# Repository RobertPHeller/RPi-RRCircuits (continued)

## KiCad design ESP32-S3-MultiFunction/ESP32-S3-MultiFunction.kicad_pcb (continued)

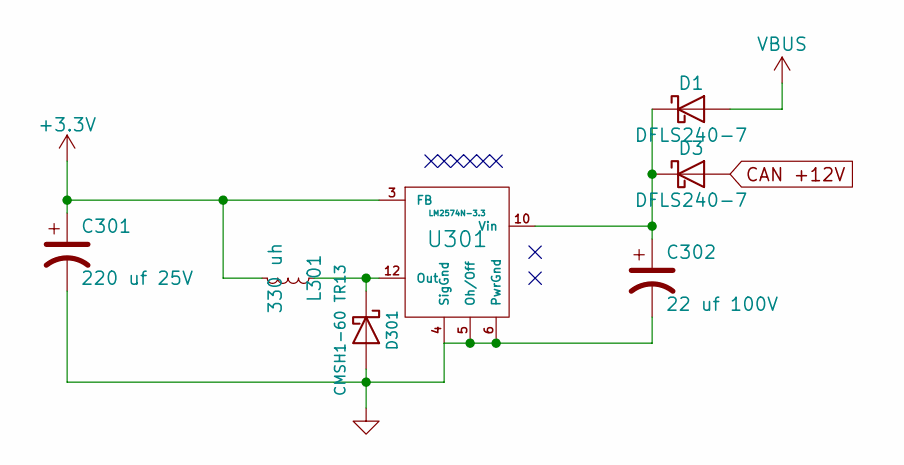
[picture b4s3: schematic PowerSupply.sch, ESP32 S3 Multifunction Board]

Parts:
C301: 220 uf 25V; CP_Elec_8x10; Mouser Part Number 647-UWT1E221MNL1GS
C302: 22 uf 100V; CP_Elec_8x10; Mouser Part Number 647-UUX2A220MNL6GS
D1, D3: DFLS240-7; D_PowerDI-123; Mouser Part Number 621-DFLS240-7
D301: CMSH1-60 TR13; D_SMB; Mouser Part Number 610-CMSH1-60TR13
L301: 330 uh; SRN1060; Mouser Part Number 652-SRN1060-331M
U301: LM2574N-3.3; SOIC-14_7.4x8.7mm_Pitch1.27mm; Mouser Part Number 926-LM2574MX33NOPB

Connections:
CAN +12V: D3.2 (A); also elsewhere on the board
GND: C301.2, C302.2, D301.2 (A), U301.4 (SigGnd), U301.5 (Oh/Off), U301.6 (PwrGnd); also elsewhere on the board
unnamed: C302.1, D1.1 (K), D3.1 (K), U301.10 (Vin)
unnamed: D301.1 (K), L301.1, U301.12 (Out)
VBUS: D1.2 (A); also elsewhere on the board

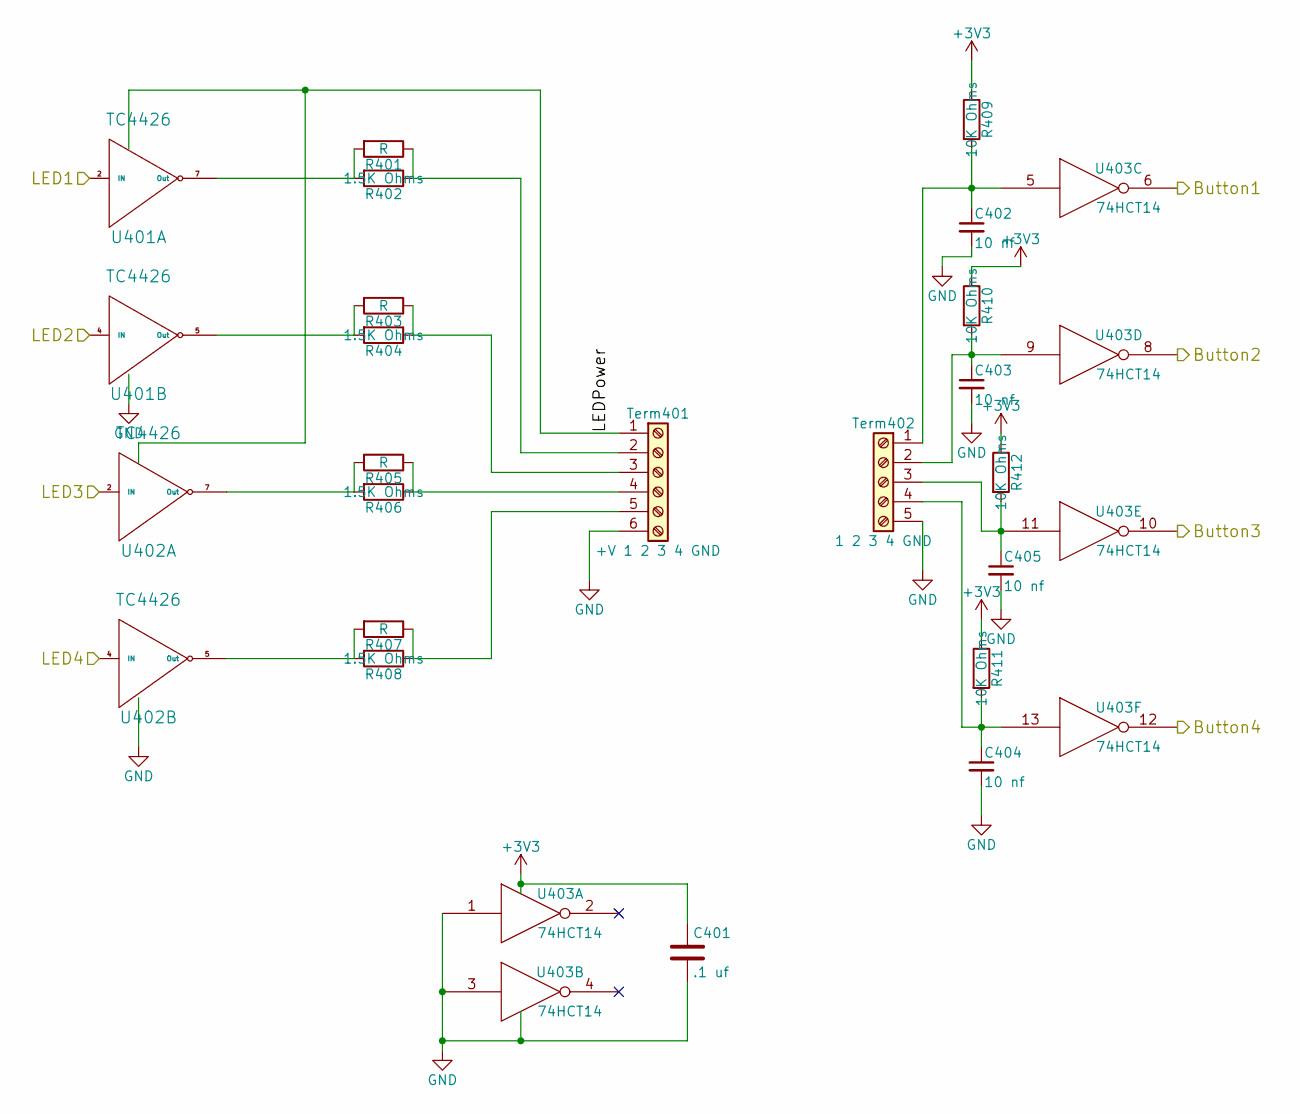
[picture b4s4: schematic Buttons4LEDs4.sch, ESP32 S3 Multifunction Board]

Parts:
C401: .1 uf; C_0603; Mouser Part Number 710-885012206095
C402, C403, C404, C405: 10 nf; C_0603; Mouser Part Number 710-885382206002
R401, R403, R405, R407: R; R_Axial_DIN0207_L6.3mm_D2.5mm_P7.62mm_Horizontal
R402, R404, R406, R408: 1.5K Ohms; R_0603; Mouser Part Number 71-CRCW06031K50JNEAC
R409, R410, R411, R412: 10K Ohms; R_0603; Mouser Part Number 71-CRCW060310K0JNEBC
Term401: +V 1 2 3 4 GND; TerminalBlock_Pheonix_MPT-2.54mm_6pol; Mouser Part Number 651-1725698
Term402: 1 2 3 4 GND; TerminalBlock_Pheonix_MPT-2.54mm_5pol; Mouser Part Number 651-1725685
U401, U402: TC4426; SOIC-8_3.9x4.9mm_Pitch1.27mm; Mouser Part Number 579-TC1426COA713
U403: 74HCT14; SOIC-14_3.9x8.7mm_Pitch1.27mm; Mouser Part Number 595-CD74HC14M

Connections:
/Buttons and LEDs/Button1: U403.6; also elsewhere on the board
/Buttons and LEDs/Button2: U403.8; also elsewhere on the board
/Buttons and LEDs/Button3: U403.10; also elsewhere on the board
/Buttons and LEDs/Button4: U403.12; also elsewhere on the board
/ESP32 MCU/GPIO1(LEDS4): U402.4 (IN); also elsewhere on the board
/ESP32 MCU/GPIO17(LEDS1): U401.2 (IN); also elsewhere on the board
/ESP32 MCU/GPIO18(LEDS2): U401.4 (IN); also elsewhere on the board
/ESP32 MCU/GPIO21(LEDS3): U402.2 (IN); also elsewhere on the board
GND: C401.2, C402.2, C403.2, C404.2, C405.2, Term401.6, Term402.5, U401.3 (GND), U402.3 (GND), U403.1, U403.3, U403.7 (GND); also elsewhere on the board
unnamed: C402.1, R409.2, Term402.1, U403.5
unnamed: C403.1, R410.2, Term402.2, U403.9
unnamed: C404.1, R411.2, Term402.4, U403.13
unnamed: C405.1, R412.2, Term402.3, U403.11
unnamed: R401.1, R402.1, Term401.2
unnamed: R401.2, R402.2, U401.7 (Out)
unnamed: R403.1, R404.1, Term401.3
unnamed: R403.2, R404.2, U401.5 (Out)
unnamed: R405.1, R406.1, Term401.4
unnamed: R405.2, R406.2, U402.7 (Out)
unnamed: R407.1, R408.1, Term401.5
unnamed: R407.2, R408.2, U402.5 (Out)
VPower: Term401.1, U401.6 (VPower), U402.6 (VPower)

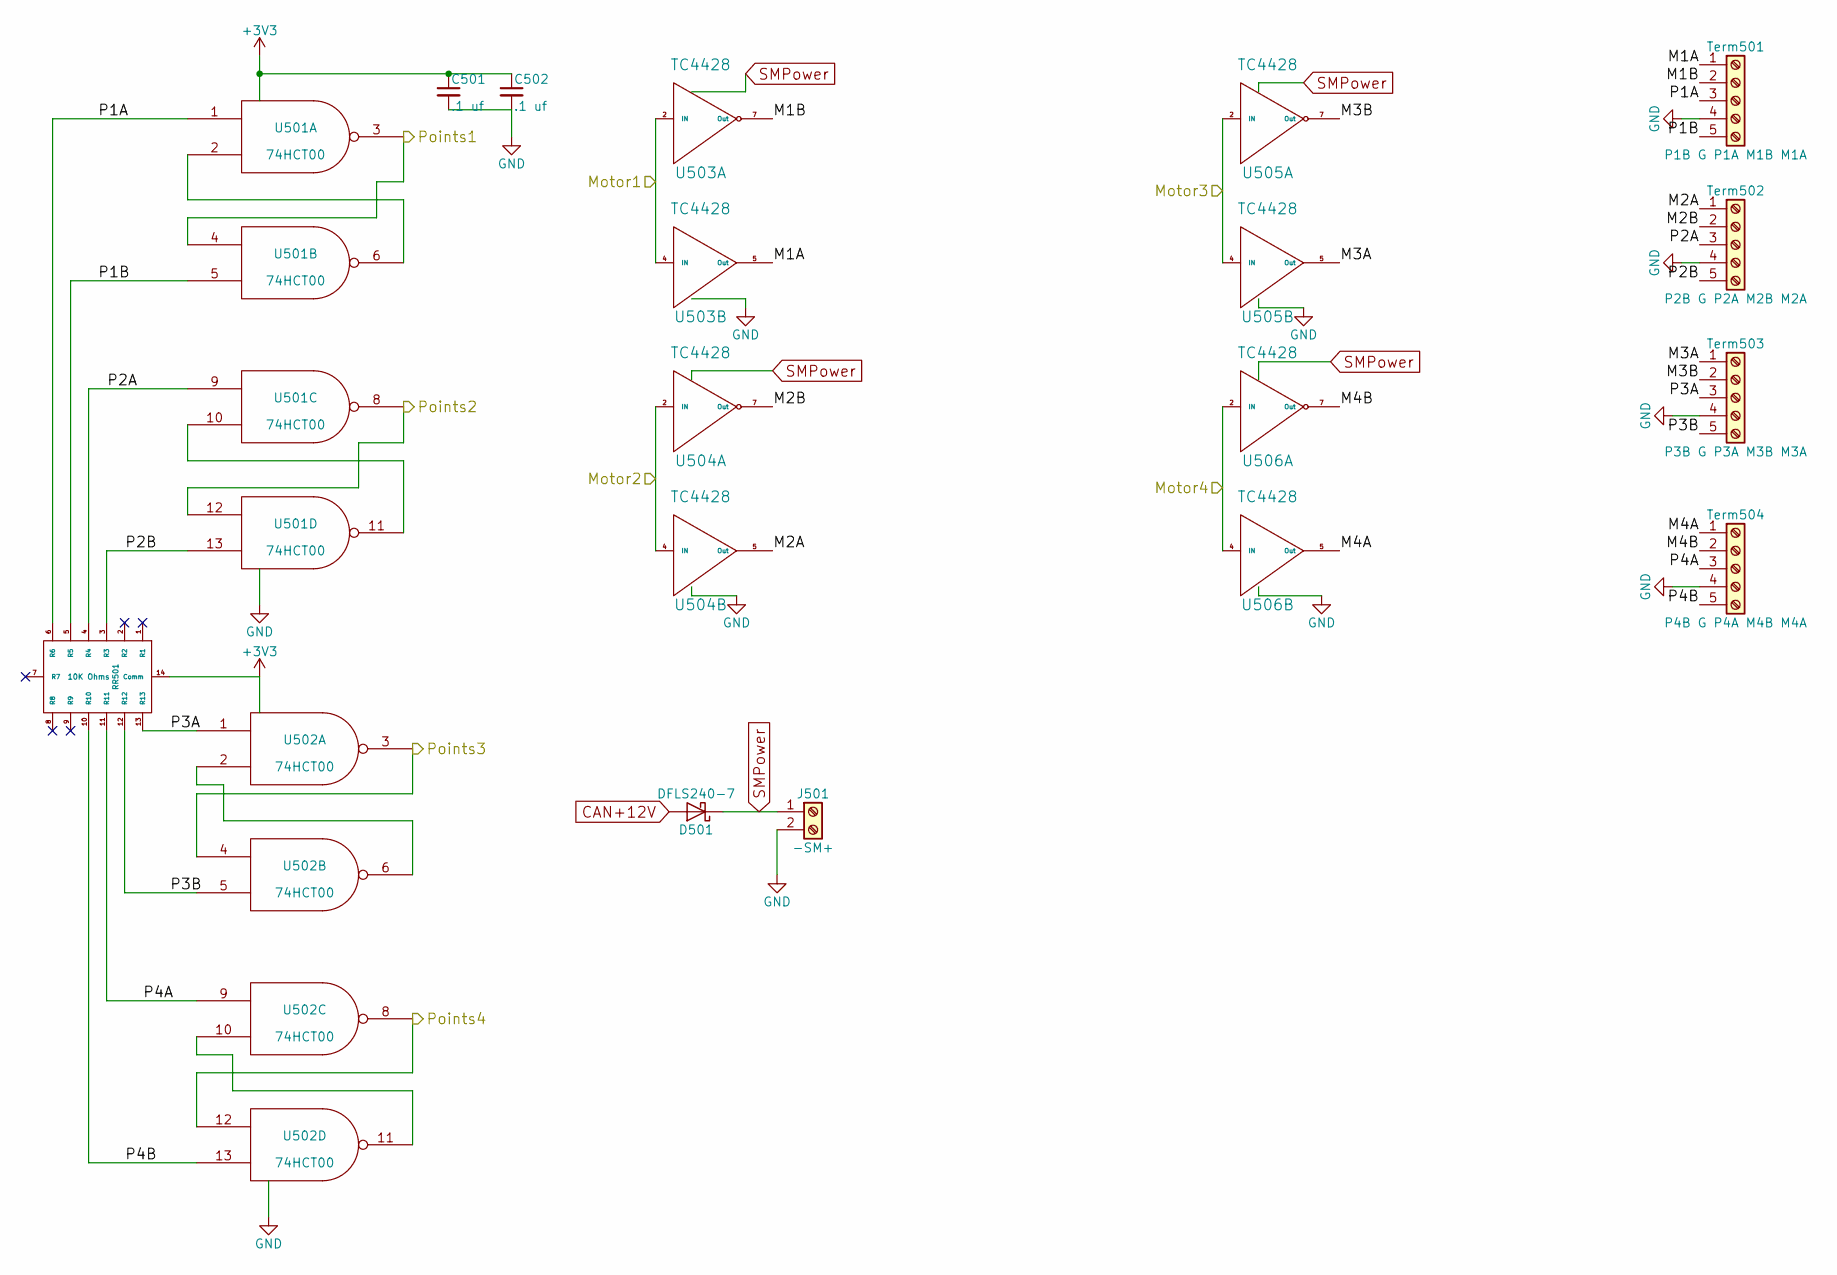
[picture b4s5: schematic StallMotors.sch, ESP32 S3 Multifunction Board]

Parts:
C501, C502: .1 uf; C_0603; Mouser Part Number 710-885012206095
D501: DFLS240-7; D_PowerDI-123; Mouser Part Number 621-DFLS240-7
J501: -SM+; TerminalBlock_Pheonix_MPT-2.54mm_2pol; Mouser Part Number 651-172565
RR501: 10K Ohms; 4814P; Mouser Part Number 652-4814P-2LF-10K
Term501: P1B G P1A M1B M1A; TerminalBlock_Pheonix_MPT-2.54mm_5pol; Mouser Part Number 651-1725685
Term502: P2B G P2A M2B M2A; TerminalBlock_Pheonix_MPT-2.54mm_5pol; Mouser Part Number 651-1725685
Term503: P3B G P3A M3B M3A; TerminalBlock_Pheonix_MPT-2.54mm_5pol; Mouser Part Number 651-1725685
Term504: P4B G P4A M4B M4A; TerminalBlock_Pheonix_MPT-2.54mm_5pol; Mouser Part Number 651-1725685
U501, U502: 74HCT00; SOIC-14_3.9x8.7mm_Pitch1.27mm; Mouser Part Number 595-SN74AHC00D
U503, U504, U505, U506: TC4428; SOIC-8_3.9x4.9mm_Pitch1.27mm; Mouser Part Number 579-TC4428VOA

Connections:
/ESP32 MCU/GPIO8(Motor3): U505.2 (IN), U505.4 (IN); also elsewhere on the board
/ESP32 MCU/GPIO9(Motor1): U503.2 (IN), U503.4 (IN); also elsewhere on the board
/ESP32 MCU/GPIO10(Points4): U502.8, U502.12; also elsewhere on the board
/ESP32 MCU/GPIO11(Motor2): U504.2 (IN), U504.4 (IN); also elsewhere on the board
/ESP32 MCU/GPIO12(Points1): U501.3, U501.4; also elsewhere on the board
/ESP32 MCU/GPIO13(Points2): U501.8, U501.12; also elsewhere on the board
/ESP32 MCU/GPIO14(Points3): U502.3, U502.4; also elsewhere on the board
/ESP32 MCU/GPIO39(Motor4): U506.2 (IN), U506.4 (IN); also elsewhere on the board
/Stall Motors/M1A: Term501.1, U503.5 (Out)
/Stall Motors/M1B: Term501.2, U503.7 (Out)
/Stall Motors/M2A: Term502.1, U504.5 (Out)
/Stall Motors/M2B: Term502.2, U504.7 (Out)
/Stall Motors/M3A: Term503.1, U505.5 (Out)
/Stall Motors/M3B: Term503.2, U505.7 (Out)
/Stall Motors/M4A: Term504.1, U506.5 (Out)
/Stall Motors/M4B: Term504.2, U506.7 (Out)
/Stall Motors/P1A: RR501.6 (R6), Term501.3, U501.1
/Stall Motors/P1B: RR501.5 (R5), Term501.5, U501.5
/Stall Motors/P2A: RR501.4 (R4), Term502.3, U501.9
/Stall Motors/P2B: RR501.3 (R3), Term502.5, U501.13
/Stall Motors/P3A: RR501.13 (R13), Term503.3, U502.1
/Stall Motors/P3B: RR501.12 (R12), Term503.5, U502.5
/Stall Motors/P4A: RR501.11 (R11), Term504.3, U502.9
/Stall Motors/P4B: RR501.10 (R10), Term504.5, U502.13
CAN +12V: D501.2 (A); also elsewhere on the board
GND: C501.2, C502.2, J501.2, Term501.4, Term502.4, Term503.4, Term504.4, U501.7 (GND), U502.7 (GND), U503.3 (GND), U504.3 (GND), U505.3 (GND), U506.3 (GND); also elsewhere on the board
unnamed: U501.2, U501.6
unnamed: U501.10, U501.11
unnamed: U502.2, U502.6
unnamed: U502.10, U502.11
SMPower: D501.1 (K), J501.1, U503.6 (Vdd), U504.6 (Vdd), U505.6 (Vdd), U506.6 (Vdd)

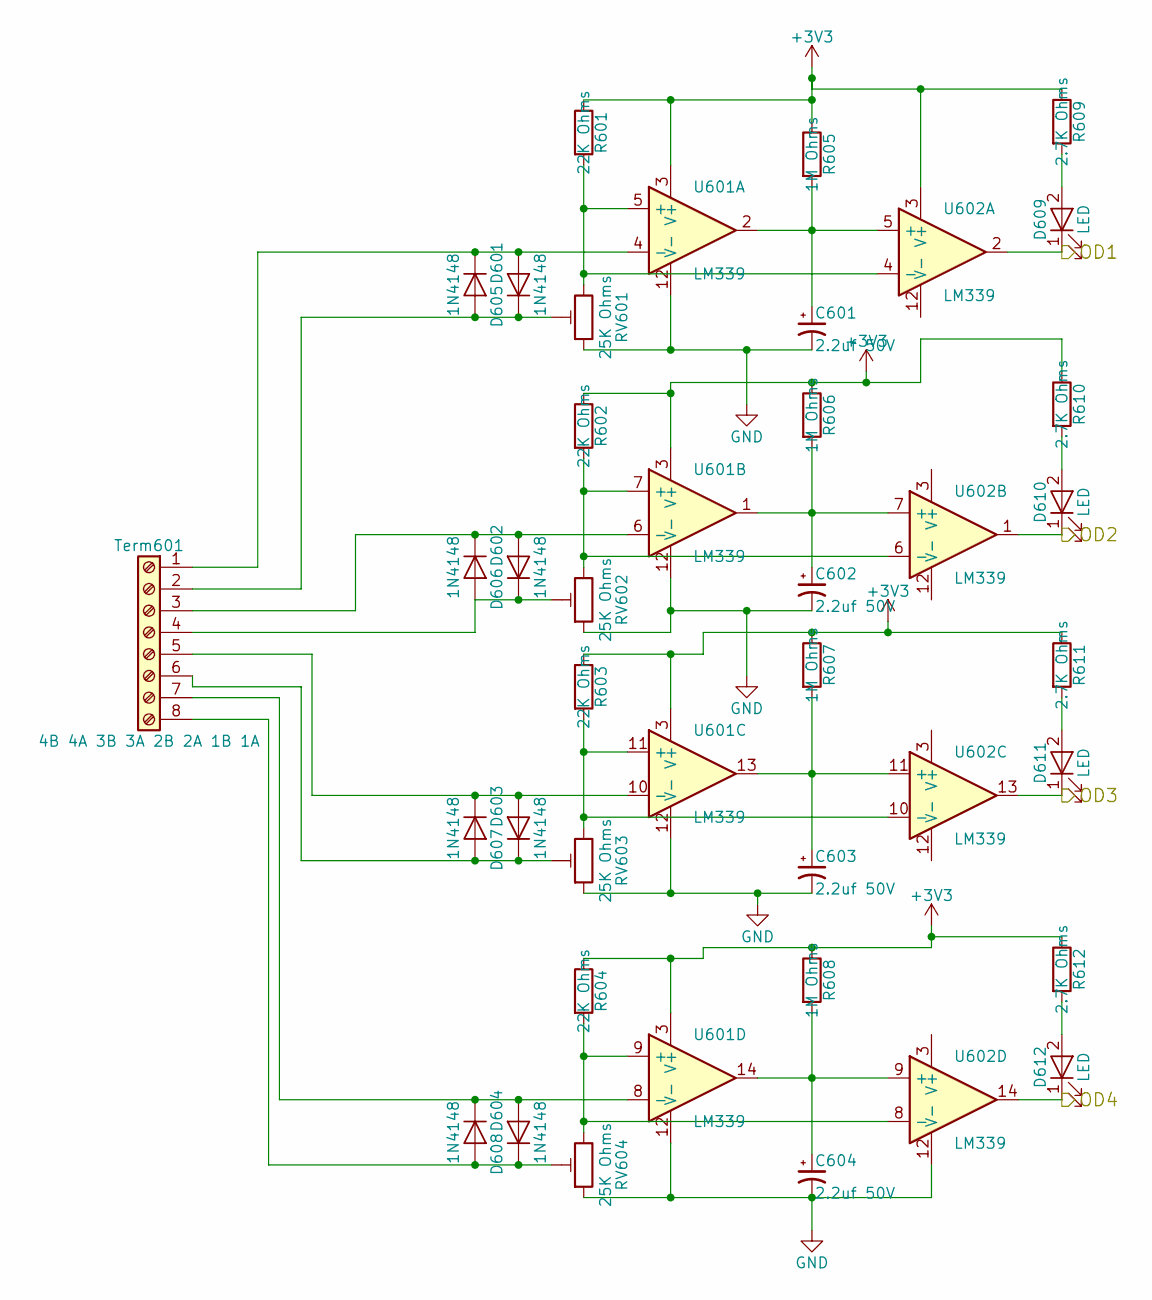
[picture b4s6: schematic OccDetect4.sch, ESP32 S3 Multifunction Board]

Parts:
C601, C602, C603, C604: 2.2uf 50V; CP_Elec_4x5.7; Mouser Part Number 710-865080140002
D601, D602, D603, D604, D605, D606, D607, D608: 1N4148; D_SOD-323; Mouser Part Number 750-1N4148WS-HF
D609, D610, D611, D612: LED; LED_0603; Mouser Part Number 710-150060SS55040
R601, R602, R603, R604: 22K Ohms; R_0603; Mouser Part Number 71-RCG060322K0JNEA
R605, R606, R607, R608: 1M Ohms; R_0603; Mouser Part Number 71-CRCW06031M00JNEAC
R609, R610, R611, R612: 2.7K Ohms; R_0603; Mouser Part Number 71-CRCW06032K70JNEAC
RV601, RV602, RV603, RV604: 25K Ohms; Potentiometer_Trimmer_Bourns_3214J; Mouser Part Number 652-3314J-1-253E
Term601: 4B 4A 3B 3A 2B 2A 1B 1A; TerminalBlock_Pheonix_MPT-2.54mm_8pol; Mouser Part Number 651-1725711
U601, U602: LM339; SOIC-14_3.9x8.7mm_Pitch1.27mm; Mouser Part Number 595-LM339DR

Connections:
/ESP32 MCU/GPIO7(OD4): D612.1 (K), U602.14; also elsewhere on the board
/ESP32 MCU/GPIO35(OD2): D610.1 (K), U602.1; also elsewhere on the board
/ESP32 MCU/GPIO36(OD3): D611.1 (K), U602.13; also elsewhere on the board
/ESP32 MCU/GPIO40(OD1): D609.1 (K), U602.2; also elsewhere on the board
GND: C601.2, C602.2, C603.2, C604.2, RV601.1, RV602.1, RV603.1, RV604.1, U601.12 (V-), U602.12 (V-); also elsewhere on the board
unnamed: C601.1, R605.2, U601.2, U602.5 (+)
unnamed: C602.1, R606.2, U601.1, U602.7 (+)
unnamed: C603.1, R607.2, U601.13, U602.11 (+)
unnamed: C604.1, R608.2, U601.14, U602.9 (+)
unnamed: D601.1 (K), D605.2 (A), Term601.1, U601.4 (-)
unnamed: D601.2 (A), D605.1 (K), RV601.2, Term601.2
unnamed: D602.1 (K), D606.2 (A), Term601.3, U601.6 (-)
unnamed: D602.2 (A), D606.1 (K), RV602.2, Term601.4
unnamed: D603.1 (K), D607.2 (A), Term601.5, U601.10 (-)
unnamed: D603.2 (A), D607.1 (K), RV603.2, Term601.6
unnamed: D604.1 (K), D608.2 (A), Term601.7, U601.8 (-)
unnamed: D604.2 (A), D608.1 (K), RV604.2, Term601.8
unnamed: D609.2 (A), R609.2
unnamed: D610.2 (A), R610.2
unnamed: D611.2 (A), R611.2
unnamed: D612.2 (A), R612.2
unnamed: R601.2, RV601.3, U601.5 (+), U602.4 (-)
unnamed: R602.2, RV602.3, U601.7 (+), U602.6 (-)
unnamed: R603.2, RV603.3, U601.11 (+), U602.10 (-)
unnamed: R604.2, RV604.3, U601.9 (+), U602.8 (-)

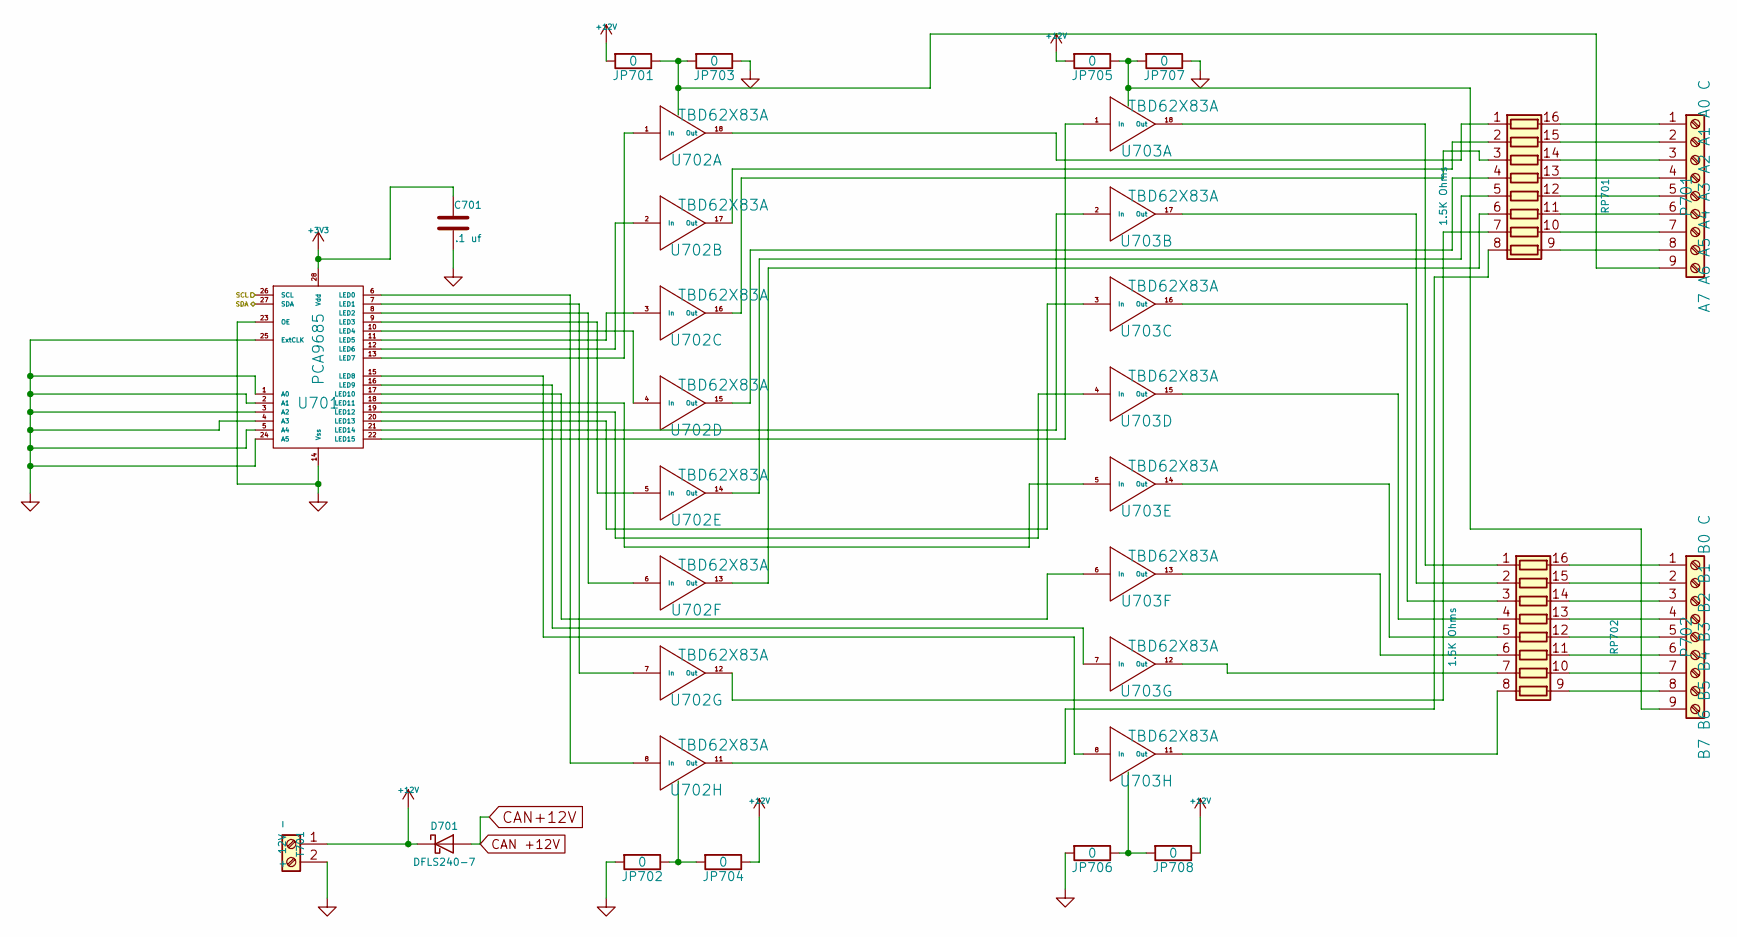
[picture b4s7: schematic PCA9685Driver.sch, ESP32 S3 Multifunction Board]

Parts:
C701: .1 uf; C_0603; Mouser Part Number 710-885012206095
D701: DFLS240-7; D_PowerDI-123; Mouser Part Number 621-DFLS240-7
JP701, JP702, JP703, JP704, JP705, JP706, JP707, JP708: 0; R_1206; Mouser Part Number 71-CRCW12060000Z0EBC
P701: A7 A6 A5 A4 A3 A2 A1 A0 C; TerminalBlock_Pheonix_MPT-2.54mm_9pol; Mouser Part Number 651-1725724
P702: B7 B6 B5 B4 B3 B2 B1 B0 C; TerminalBlock_Pheonix_MPT-2.54mm_9pol; Mouser Part Number 651-1725724
RP701, RP702: 1.5K Ohms; 4816P; Mouser Part Number 652-4816P-T1LF-1.5K
T701: + 12V -; TerminalBlock_Pheonix_MPT-2.54mm_2pol; Mouser Part Number 651-1725656
U701: PCA9685; TSSOP-28_4.4x9.7mm_Pitch0.65mm; Mouser Part Number 771-PCA9685PW,118
U702, U703: TBD62X83A; SOIC-18W_7.5x11.6mm_Pitch1.27mm; Mouser Part Number 757-TBD62083AFG or 757-TBD62783AFG

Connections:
+12V: D701.1 (K), JP701.2, JP704.1, JP705.2, JP708.1, T701.1
/ESP32 MCU/SCL: U701.26 (SCL); also elsewhere on the board
/ESP32 MCU/SDA: U701.27 (SDA); also elsewhere on the board
CAN +12V: D701.2 (A); also elsewhere on the board
GND: C701.2, JP702.2, JP703.1, JP706.2, JP707.1, T701.2, U701.1 (A0), U701.2 (A1), U701.3 (A2), U701.4 (A3), U701.5 (A4), U701.14 (Vss), U701.23 (OE), U701.24 (A5), U701.25 (ExtCLK); also elsewhere on the board
unnamed: JP701.1, JP703.2, P701.9, U702.10 (OC)
unnamed: JP702.1, JP704.2, U702.9 (IC)
unnamed: JP705.1, JP707.2, P702.9, U703.10 (OC)
unnamed: JP706.1, JP708.2, U703.9 (IC)
unnamed: P701.1, RP701.16 (R1.2)
unnamed: P701.2, RP701.15 (R2.2)
unnamed: P701.3, RP701.14 (R3.2)
unnamed: P701.4, RP701.13 (R4.2)
unnamed: P701.5, RP701.12 (R5.2)
unnamed: P701.6, RP701.11 (R6.2)
unnamed: P701.7, RP701.10 (R7.2)
unnamed: P701.8, RP701.9 (R8.2)
unnamed: P702.1, RP702.16 (R1.2)
unnamed: P702.2, RP702.15 (R2.2)
unnamed: P702.3, RP702.14 (R3.2)
unnamed: P702.4, RP702.13 (R4.2)
unnamed: P702.5, RP702.12 (R5.2)
unnamed: P702.6, RP702.11 (R6.2)
unnamed: P702.7, RP702.10 (R7.2)
unnamed: P702.8, RP702.9 (R8.2)
unnamed: RP701.1 (R1.1), U702.18 (Out)
unnamed: RP701.2 (R2.1), U702.17 (Out)
unnamed: RP701.3 (R3.1), U702.16 (Out)
unnamed: RP701.4 (R4.1), U702.15 (Out)
unnamed: RP701.5 (R5.1), U702.14 (Out)
unnamed: RP701.6 (R6.1), U702.13 (Out)
unnamed: RP701.7 (R7.1), U702.12 (Out)
unnamed: RP701.8 (R8.1), U702.11 (Out)
unnamed: RP702.1 (R1.1), U703.18 (Out)
unnamed: RP702.2 (R2.1), U703.17 (Out)
unnamed: RP702.3 (R3.1), U703.16 (Out)
unnamed: RP702.4 (R4.1), U703.15 (Out)
unnamed: RP702.5 (R5.1), U703.14 (Out)
unnamed: RP702.6 (R6.1), U703.13 (Out)
unnamed: RP702.7 (R7.1), U703.12 (Out)
unnamed: RP702.8 (R8.1), U703.11 (Out)
unnamed: U701.6 (LED0), U702.8 (In)
unnamed: U701.7 (LED1), U702.7 (In)
unnamed: U701.8 (LED2), U702.6 (In)
unnamed: U701.9 (LED3), U702.5 (In)
unnamed: U701.10 (LED4), U702.4 (In)
unnamed: U701.11 (LED5), U702.3 (In)
unnamed: U701.12 (LED6), U702.2 (In)
unnamed: U701.13 (LED7), U702.1 (In)
unnamed: U701.15 (LED8), U703.8 (In)
unnamed: U701.16 (LED9), U703.7 (In)
unnamed: U701.17 (LED10), U703.6 (In)
unnamed: U701.18 (LED11), U703.5 (In)
unnamed: U701.19 (LED12), U703.4 (In)
unnamed: U701.20 (LED13), U703.3 (In)
unnamed: U701.21 (LED14), U703.2 (In)
unnamed: U701.22 (LED15), U703.1 (In)

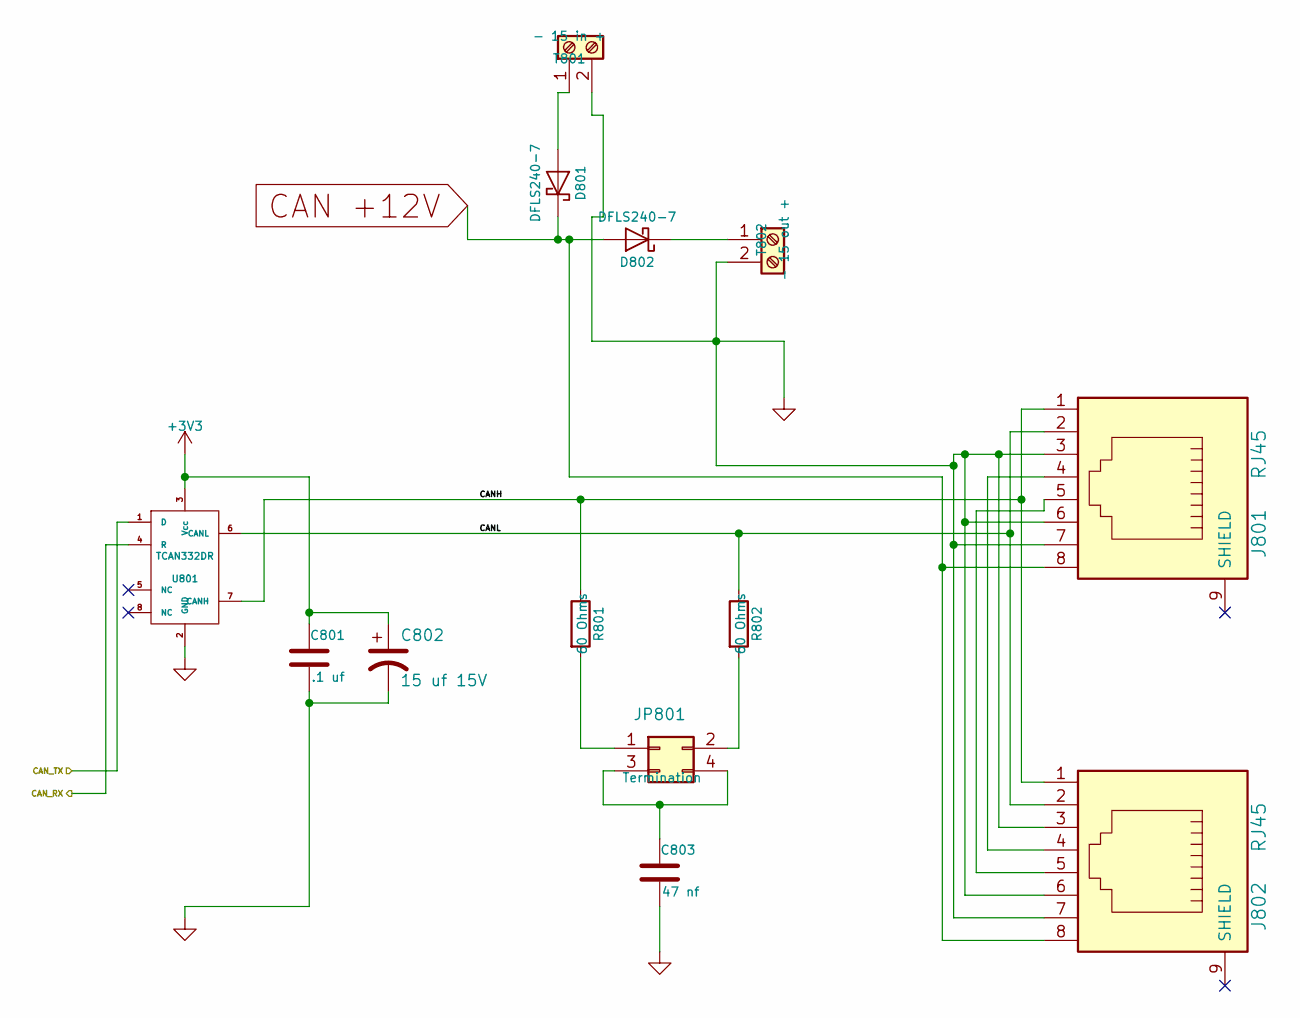
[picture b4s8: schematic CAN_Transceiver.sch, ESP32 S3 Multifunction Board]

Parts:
C801: .1 uf; C_0603; Mouser Part Number 710-885012206095
C802: 15 uf 15V; CP_Elec_4x5.7; Mouser Part Number 647-UUD1C150MCL
C803: 47 nf; C_0603; Mouser Part Number 710-885012206093
D801, D802: DFLS240-7; D_PowerDI-123; Mouser Part Number 621-DFLS240-7
J801, J802: RJ45; RJ45_8N-S; Mouser Part Number 710-615008144221
JP801: Termination; Pin_Header_Straight_2x02_Pitch2.54mm; Mouser Part Number 649-67997-404HLF
R801, R802: 60 Ohms; R_1206; Mouser Part Number 71-CRCW120660R0KNAIF
T801: - 15 in +; TerminalBlock_Pheonix_MPT-2.54mm_2pol; Mouser Part Number 651-1725656
T802: - 15 out +; TerminalBlock_Pheonix_MPT-2.54mm_2pol; Mouser Part Number 651-1725656
U801: TCAN332DR; SOIC-8_3.9x4.9mm_Pitch1.27mm; Mouser Part Number 595-TCAN332DR

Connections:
/CAN Tranceiver/CANH: J801.1, J802.1, R801.1, U801.7 (CANH)
/CAN Tranceiver/CANL: J801.2, J802.2, R802.1, U801.6 (CANL)
/CAN Tranceiver/CAN_RX: U801.4 (R); also elsewhere on the board
/CAN Tranceiver/CAN_TX: U801.1 (D); also elsewhere on the board
CAN +12V: D801.1 (K), D802.2 (A), J801.8, J802.8; also elsewhere on the board
GND: C801.2, C802.2, C803.2, J801.3, J801.6, J801.7, J802.3, J802.6, J802.7, T801.2, T802.2, U801.2 (GND); also elsewhere on the board
unnamed: C803.1, JP801.3, JP801.4
unnamed: D801.2 (A), T801.1
unnamed: D802.1 (K), T802.1
unnamed: J801.4, J802.4
unnamed: J801.5, J802.5
unnamed: JP801.1, R801.2
unnamed: JP801.2, R802.2

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
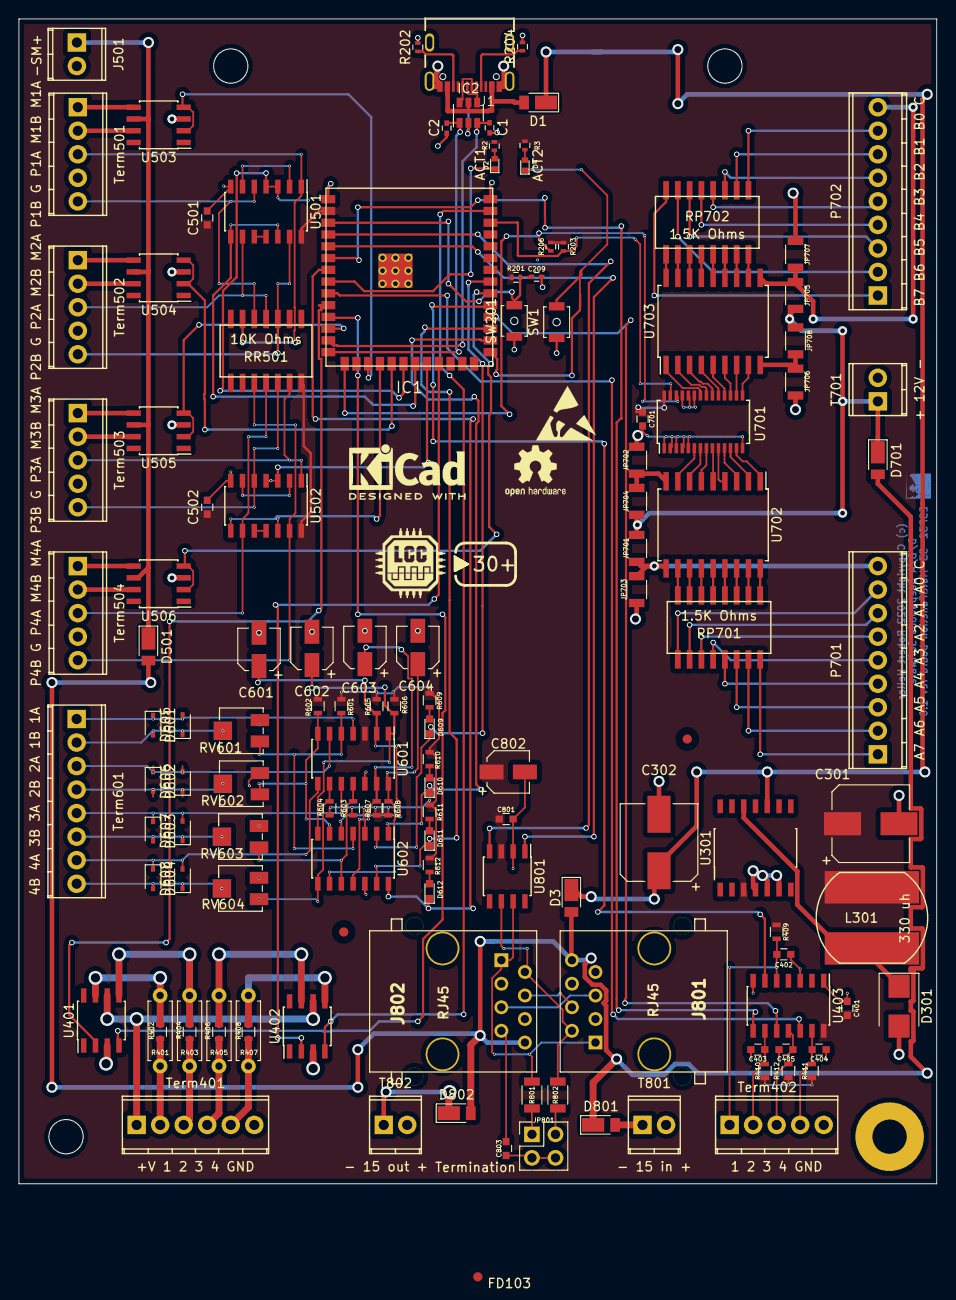
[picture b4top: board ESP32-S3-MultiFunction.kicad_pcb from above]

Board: 2 copper layers, 99.1 x 125.7 mm, 134 parts (0 on the bottom side), 157 nets.

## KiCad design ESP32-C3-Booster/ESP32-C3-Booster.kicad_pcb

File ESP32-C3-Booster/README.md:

# ESP32-C3-Booster

ESP32 C3 based DCC Booster.  This booster should work with any LCC command 
station that puts the DCC Signal out on pins 4 and 5 ("Alt") of the LCC 
network bus.

* [Mouser Cart](https://www.mouser.com/ProjectManager/ProjectDetail.aspx?AccessID=9b2d7ed72c)
* [Schematic PDF](https://github.com/RobertPHeller/RPi-RRCircuits/blob/master/ESP32-C3-Booster/ESP32-C3-Booster.pdf)
* [Board Rendering](https://github.com/RobertPHeller/RPi-RRCircuits/blob/master/ESP32-C3-Booster/ESP32-C3-Booster.png)
* [Node Firmware](https://github.com/RobertPHeller/RPi-RRCircuits/tree/master/ESP32-C3-BoosterOpenMRNIDF)

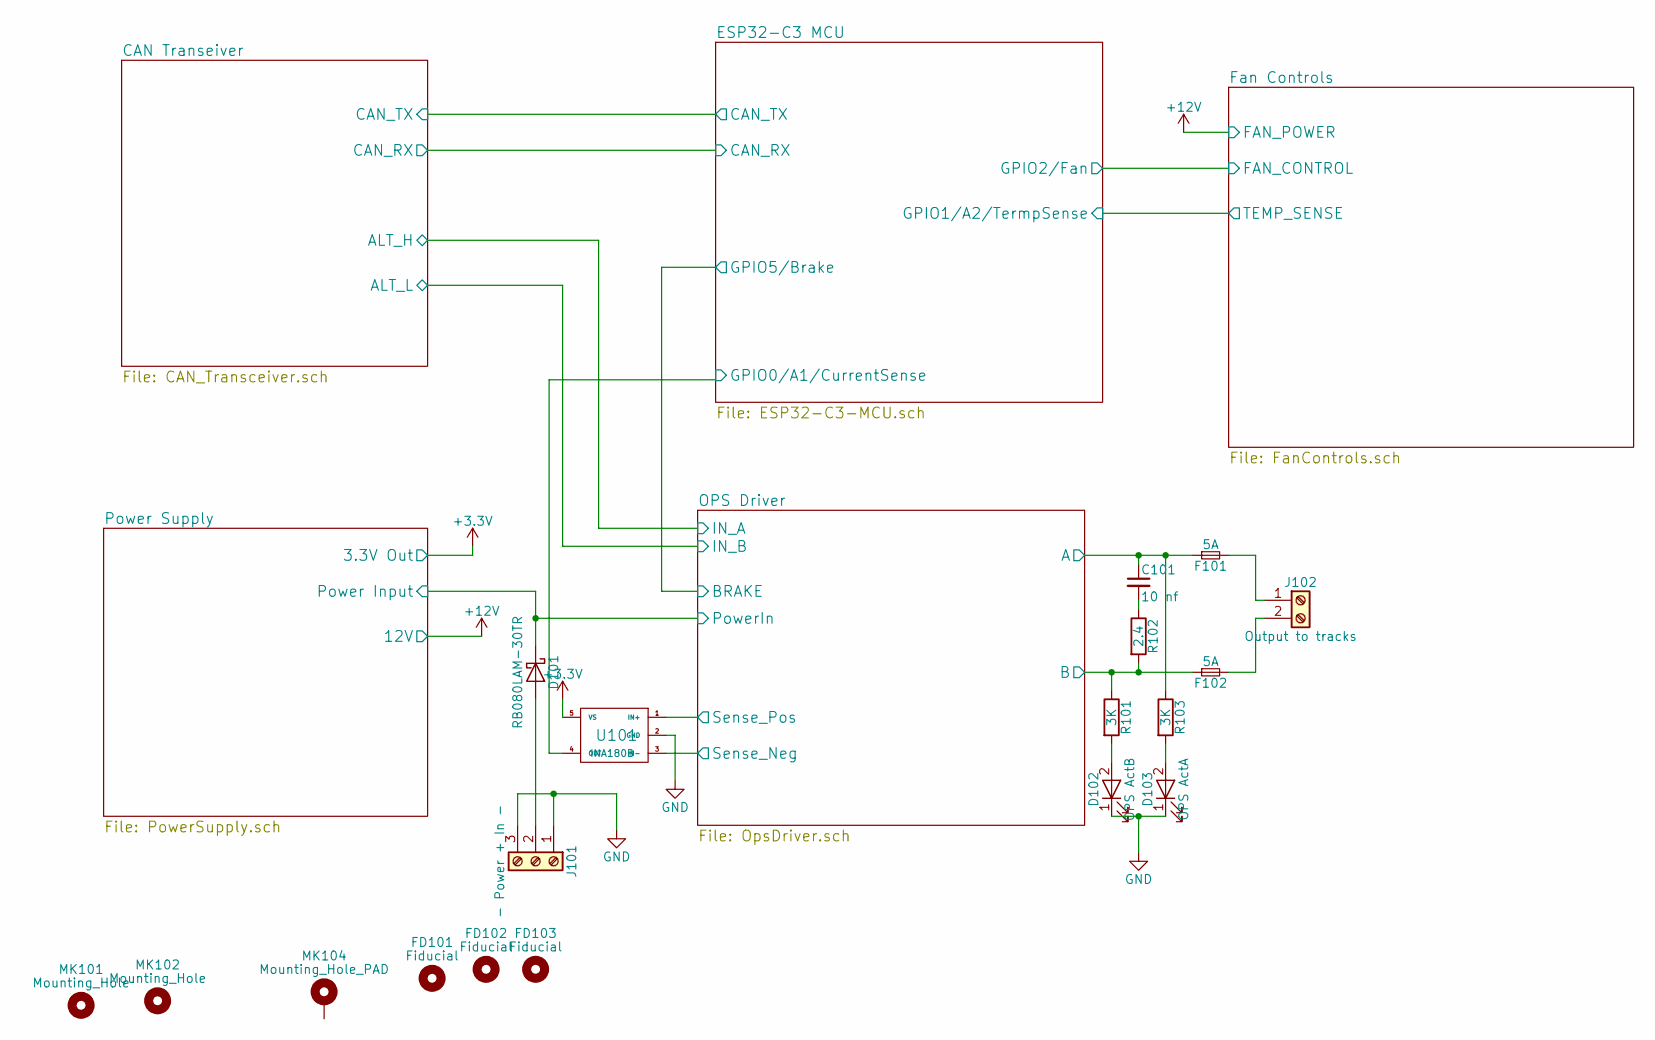
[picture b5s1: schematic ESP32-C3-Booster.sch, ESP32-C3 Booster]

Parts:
C101: 10 nf; C_1206; Mouser Part Number 791-1206B103K500CT
D101: RB080LAM-30TR; PMDTM; Mouser Part Number 755-RB080LAM-30TR
D102: OPS ActB; LED_0603; Mouser Part Number 710-150060RS75000
D103: OPS ActA; LED_0603; Mouser Part Number 710-150060GS75000
F101, F102: 5A; MFR500; Mouser Part Number 652-MFR500
FD101, FD102, FD103: Fiducial; Fiducial_classic_Small_SilkscreenTop_Type1
J101: - Power + In -; TerminalBlock_Pheonix_PT-3.5mm_3pol; Mouser Part Number 651-544225
J102: Output to tracks; TerminalBlock_Pheonix_PT-3.5mm_2pol; Mouser Part Number 651-5442248
MK101, MK102: Mounting_Hole; MountingHole_3.5mm
MK104: Mounting_Hole_PAD; MountingHole_3.5mm_Pad
R101, R103: 3K; R_0603; Mouser Part Number 660-RN73H1JT3001F100
R102: 2.4; R_1206; Mouser Part Number 71-CRCW12062R40FKEA
U101: INA180B; SOT-23-5; Mouser Part Number 595-INA180B3IDBVR

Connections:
+3V3: U101.5 (VS); also elsewhere on the board
/ESP32-C3 MCU/GPIO0/A1/CurrentSense: U101.4 (OUT); also elsewhere on the board
/OPS Driver/A: C101.1, F101.1, R103.1; also elsewhere on the board
/OPS Driver/B: F102.1, R101.1, R102.2; also elsewhere on the board
/OPS Driver/Sense_Neg: U101.3 (IN-); also elsewhere on the board
/Power Supply/Power Input: D101.1 (K), U101.1 (IN+); also elsewhere on the board
GND: D102.1 (K), D103.1 (K), J101.1, J101.3, U101.2 (GND); also elsewhere on the board
unnamed: C101.2, R102.1
unnamed: D101.2 (A), J101.2
unnamed: D102.2 (A), R101.2
unnamed: D103.2 (A), R103.2
unnamed: F101.2, J102.1
unnamed: F102.2, J102.2
